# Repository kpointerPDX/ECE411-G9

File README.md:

# ECE411-G9
Public repository for ECE-411 Group 9 @ PSU, 2022.

Gantt Chart for project tracking: https://sharing.clickup.com/42085151/g/h/184arz-80/8154f2cd82b7851

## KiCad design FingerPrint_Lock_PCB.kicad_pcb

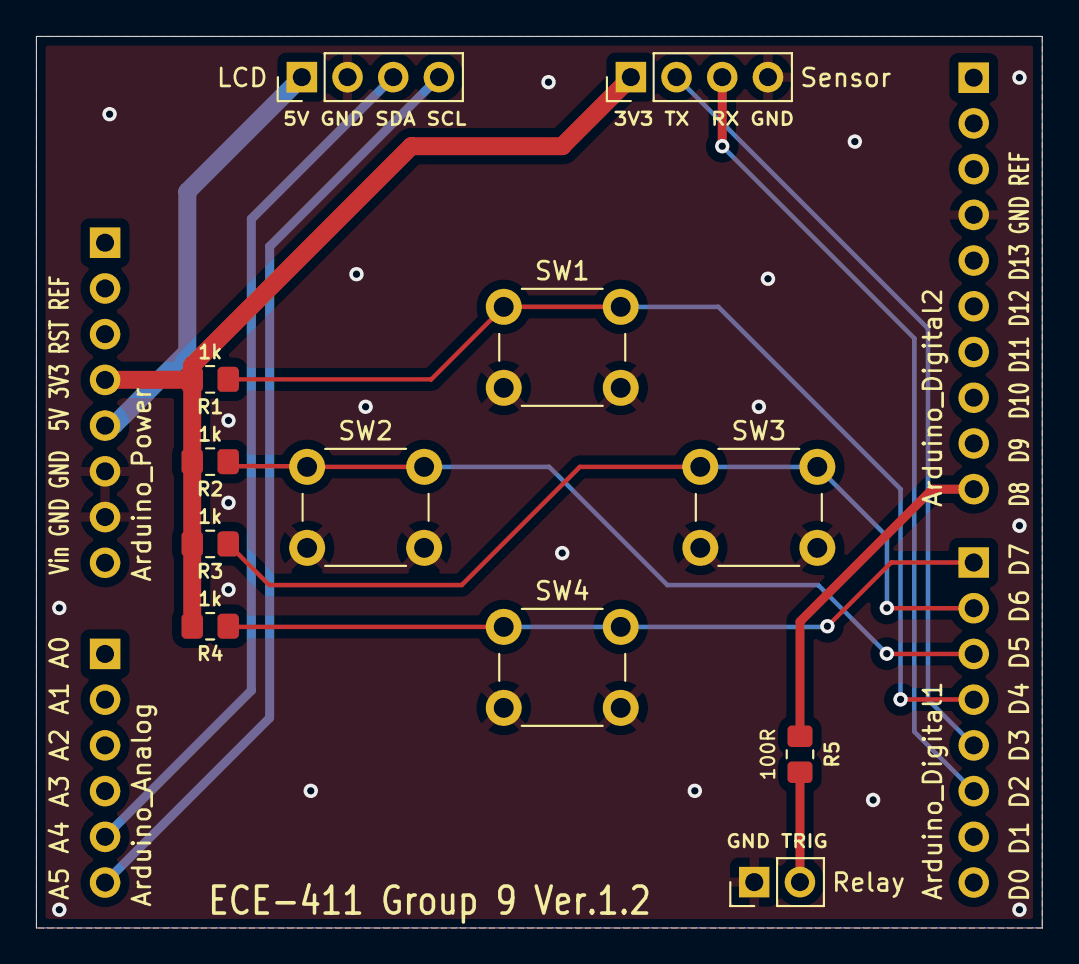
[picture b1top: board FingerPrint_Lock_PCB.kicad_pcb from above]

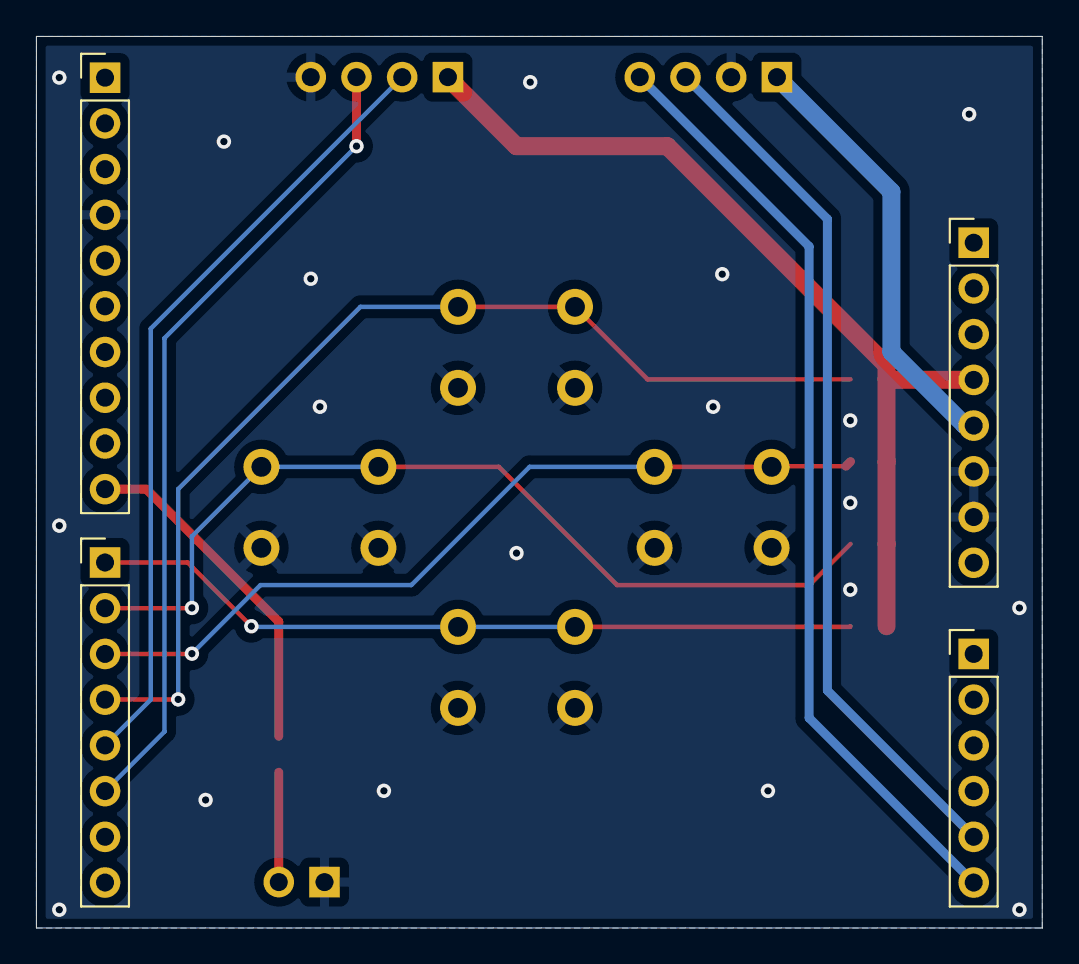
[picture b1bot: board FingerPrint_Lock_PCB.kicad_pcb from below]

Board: 2 copper layers, 55.9 x 49.5 mm, 16 parts (4 on the bottom side), 13 nets.

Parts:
J1: Arduino_Digital1; PinHeader_1x08_P2.54mm_Vertical
J2: Arduino_Digital2; PinHeader_1x10_P2.54mm_Vertical
J3: Arduino_Analog; PinHeader_1x06_P2.54mm_Vertical
J4: Arduino_Power; PinHeader_1x08_P2.54mm_Vertical
J5: Sensor; PinHeader_1x04_P2.54mm_Vertical
J6: Relay; PinHeader_1x02_P2.54mm_Vertical
J7: LCD; PinHeader_1x04_P2.54mm_Vertical
R1, R2, R3, R4: 1k; R_0805_2012Metric_Pad1.20x1.40mm_HandSolder
R5: 100R; R_0805_2012Metric_Pad1.20x1.40mm_HandSolder
SW1, SW2, SW3, SW4: 6x5mm; SW_PUSH_6mm_H5mm

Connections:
/3V3: J4.4, J5.1, R1.2, R2.2, R3.2, R4.2
/5V: J4.5, J7.1
/A4_SDA: J3.5, J7.3
/A5_SCL: J3.6, J7.4
/D2_RX: J1.6, J5.3
/D3_TX: J1.5, J5.2
/D4: J1.4, R1.1, SW1.1
/D5: J1.3, R2.1, SW2.1
/D6: J1.2, R3.1, SW3.1
/D7: J1.1, R4.1, SW4.1
/D8_TRIGGER: J2.10, R5.2
/RELAY_IN: J6.2, R5.1
GND: J2.4, J4.6, J4.7, J5.4, J6.1, J7.2, SW1.2, SW2.2, SW3.2, SW4.2

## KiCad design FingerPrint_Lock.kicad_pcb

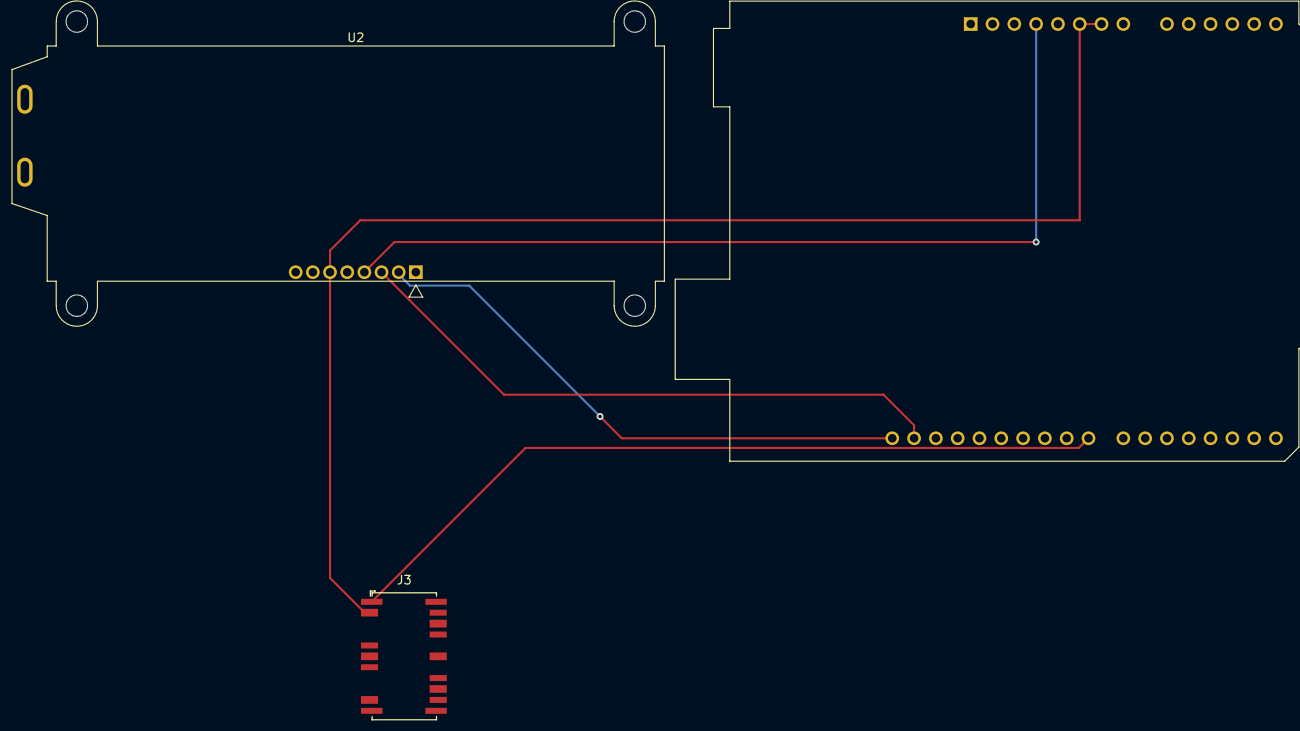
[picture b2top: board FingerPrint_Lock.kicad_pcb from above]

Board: 2 copper layers, 3 parts (0 on the bottom side), 5 nets.

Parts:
A1: Arduino_UNO_R3
J3: 12V Relay; Relay_SPDT_AXICOM_HF3Series_50ohms_Pitch1.27mm
U2: I2C 2X16 LCD; NHD-C0220BiZ

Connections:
unnamed: A1.4 (3V3), U2.4 (VSS)
unnamed: A1.6 (GND), A1.7 (GND), J3.2, U2.6 (GND)
unnamed: A1.23 (D8), J3.1
unnamed: A1.31 (SDA/A4), U2.3 (SDA)
unnamed: A1.32 (SCL/A5), U2.2 (SCL)

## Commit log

2022-10-27 initial upload
2022-10-27 mistaken upload
2022-10-27 name correction
2022-11-10 Add files via upload
    Functional decomposition of device and components.
2022-11-10 Add files via upload
    Corrected connections and labels. Added 4th button.
2022-11-14 Final(?) schematics/PCB upload
    Final(?) version of overview schematic, PCB file, and PCB Schematic.
2022-11-15 Post-design-review revisions
2022-11-15 Schematic files unified; original now deprecated
2022-11-16 Minor changes; updated silkscreen
2022-11-22 Create Interface.ino
    Initial Button/LCD User interface.
2022-12-01 Initial upload: PDF version of overall schematic
2022-12-05 beginning integration
2022-12-06 Initial integrated SW upload
    Includes the code from "Interface.ino"
2022-12-08 Added 3d model files for chassis
2022-12-08 Added demo videos
